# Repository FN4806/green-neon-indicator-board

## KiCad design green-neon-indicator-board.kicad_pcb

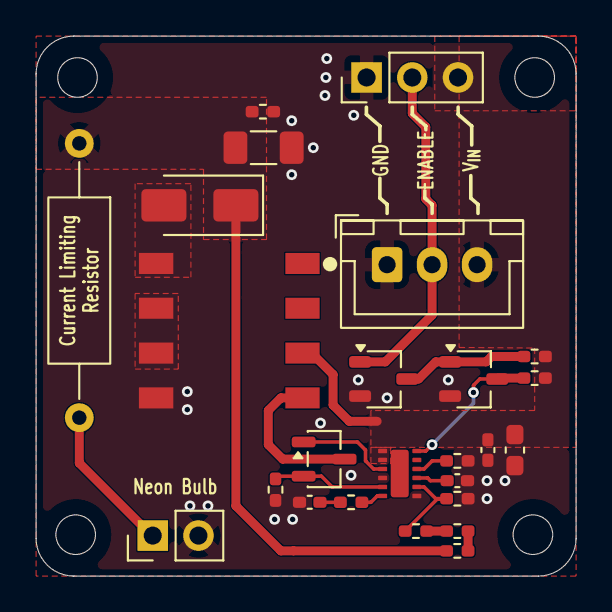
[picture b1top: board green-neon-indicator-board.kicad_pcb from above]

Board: 2 copper layers, 30.0 x 30.0 mm, 25 parts (0 on the bottom side), 19 nets.

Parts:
C1: 10u; C_0603_1608Metric_Pad1.08x0.95mm_HandSolder
C2, C3: 100n; C_0402_1005Metric_Pad0.74x0.62mm_HandSolder
C4: 470n; C_0402_1005Metric_Pad0.74x0.62mm_HandSolder
C5: 100n; C_1206_3216Metric_Pad1.33x1.80mm_HandSolder
D1: US1G-E3/61T; D_SMA
J1: 1x3 THT Headers; PinHeader_1x03_P2.54mm_Vertical
J2: JST XH Compatible; JST_XH_B3B-XH-A_1x03_P2.50mm_Vertical
NE1: Green Neon Lamp; PinHeader_1x02_P2.54mm_Vertical
Q1: IRLML0100TRPBF; SOT-23-3
Q2, Q3: PJA138K; TSOT-23
R3: 110k; R_0402_1005Metric_Pad0.72x0.64mm_HandSolder
R4, R9, R12: 10k; R_0402_1005Metric_Pad0.72x0.64mm_HandSolder
R5: 0.5; R_0402_1005Metric_Pad0.72x0.64mm_HandSolder
R6, R7, R8: 499k; R_0402_1005Metric_Pad0.72x0.64mm_HandSolder
R10: 1M; R_0402_1005Metric_Pad0.72x0.64mm_HandSolder
R11: 330k; R_Axial_DIN0309_L9.0mm_D3.2mm_P15.24mm_Horizontal
R13: 100k; R_0402_1005Metric_Pad0.72x0.64mm_HandSolder
T1: WURTH_750311692
U1: LM5155

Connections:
+150V: C5.1, D1.1 (K), R6.1, R10.1, R11.1
/BOOST_EN: Q2.3 (D), R13.2, U1.12 (UVLO/EN/SYNC)
/CS: Q1.2 (S), R5.1, U1.5 (CS)
/EN_INPUT: J1.2, J2.2, Q3.1 (G)
/FB: R8.2, R9.1, U1.8 (FB)
GND: C1.2, C2.2, C3.2, C4.2, C5.2, J1.1, J2.1, NE1.2, Q2.2 (S), Q3.2 (S), R3.2, R5.2, R9.2, R10.2, T1.8 (SD), U1.4 (PGND), U1.7 (AGND)
unnamed: C4.1, R4.2
unnamed: D1.2 (A), T1.5 (SA)
unnamed: NE1.1, R11.2
unnamed: Q1.3 (D), T1.4 (AB)
unnamed: Q1.1 (G), U1.3 (GATE)
unnamed: Q2.1 (G), Q3.3 (D), R12.2
unnamed: R6.2, R7.1
unnamed: R7.2, R8.1
unnamed: T1.6 (SB), T1.7 (SC)
unnamed: R4.1, U1.6 (COMP)
unnamed: R3.1, U1.10 (RT)
unnamed: C3.1, U1.9 (SS)
V_{BIAS}: C1.1, C2.1, J1.3, J2.3, R12.1, R13.1, T1.3 (AA), U1.1 (BIAS), U1.2 (VCC)
